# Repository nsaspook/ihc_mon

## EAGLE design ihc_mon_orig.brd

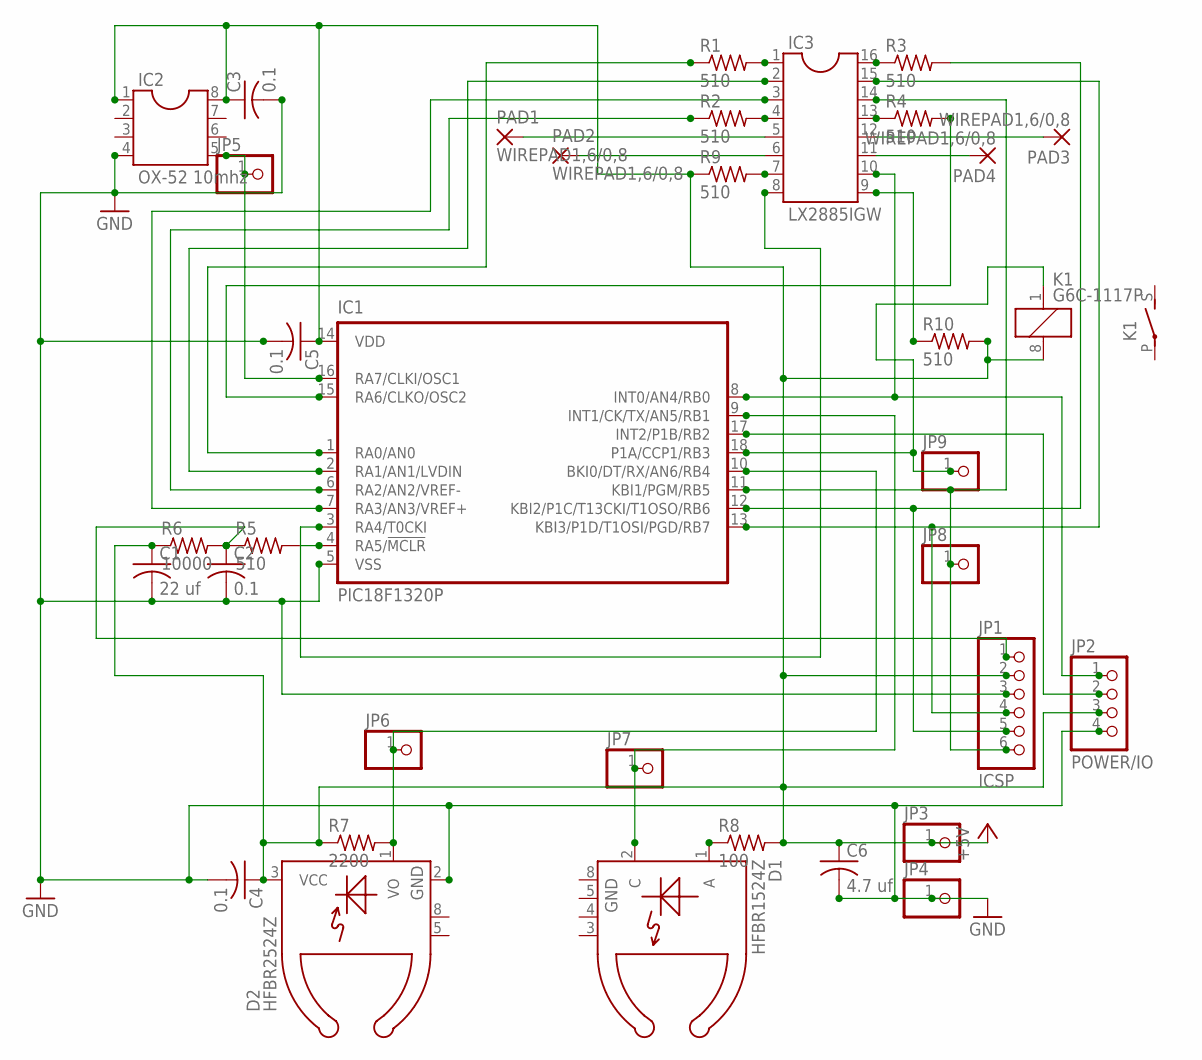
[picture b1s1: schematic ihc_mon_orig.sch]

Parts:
C1: 22 uf; C025-024X044
C2, C3, C4, C5: 0.1; C050-025X075
C6: 4.7 uf; C025-024X044
D1: HFBR1524Z; HFBR25XX
D2: HFBR2524Z; HFBR25XX
IC1: PIC18F1320P; DIL18
IC2: OX-52 10mhz; SOCKET-08
IC3: LX2885IGW; SOCKET-16
JP1: ICSP; 1X06
JP2: POWER/IO; 1X04
JP3, JP4, JP5, JP6, JP7, JP8, JP9: PINHD-1X1; 1X01
K1: G6C-1117P
PAD1, PAD2, PAD3, PAD4: WIREPAD1,6/0,8; 1,6/0,8
R1, R2, R3, R4, R5, R9, R10: 510; 0204V
R6: 10000; 0204V
R7: 2200; 0204V
R8: 100; 0204V

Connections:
+5V: C1.1, C3.1, C4.1, C5.1, C6.1, D2.3 (VCC), IC1.14 (VDD), IC2.1, IC2.8, JP1.2, JP2.3, JP3.1, K1.8 (2), R6.1, R7.1, R8.2, R9.1, R10.2
GND: C1.2, C2.2, C3.2, C4.2, C5.2, C6.2, D2.2 (GND), IC1.5 (VSS), IC2.4, JP1.3, JP2.4, JP4.1
unnamed: IC3.1, R1.2
unnamed: IC3.4, R2.2
unnamed: IC3.16, R3.1
unnamed: IC3.13, R4.1
unnamed: IC1.4 (RA5/!MCLR), R5.2
unnamed: C2.1, JP1.1, R5.1, R6.2
unnamed: D2.1 (VO), IC1.10 (BKI0/DT/RX/AN6/RB4), JP6.1, R7.2
unnamed: D1.1 (A), R8.1
unnamed: IC3.7, R9.2
unnamed: IC1.18 (P1A/CCP1/RB3), JP9.1, K1.1
unnamed: IC1.8 (INT0/AN4/RB0), IC3.10, JP2.1
unnamed: IC3.9, R10.1
unnamed: IC3.5, PAD1.1
unnamed: D1.2 (C), IC1.9 (INT1/CK/TX/AN5/RB1), JP7.1
unnamed: IC1.11 (KBI1/PGM/RB5), IC3.14, JP1.6, JP8.1
unnamed: IC1.1 (RA0/AN0), R1.1
unnamed: IC1.2 (RA1/AN1/LVDIN), IC3.2
unnamed: IC1.6 (RA2/AN2/VREF-), R2.1
unnamed: IC1.7 (RA3/AN3/VREF+), IC3.3
unnamed: IC1.12 (KBI2/P1C/T13CKI/T1OSO/RB6), JP1.5, R3.2
unnamed: IC1.13 (KBI3/P1D/T1OSI/PGD/RB7), IC3.15, JP1.4
unnamed: IC1.15 (RA6/CLKO/OSC2), R4.2
unnamed: IC3.6, PAD2.1
unnamed: IC1.3 (RA4/T0CKI), IC3.8
unnamed: IC1.16 (RA7/CLKI/OSC1), IC2.5, JP5.1
unnamed: IC1.17 (INT2/P1B/RB2), JP2.2
unnamed: IC3.12, PAD3.1
unnamed: IC3.11, PAD4.1

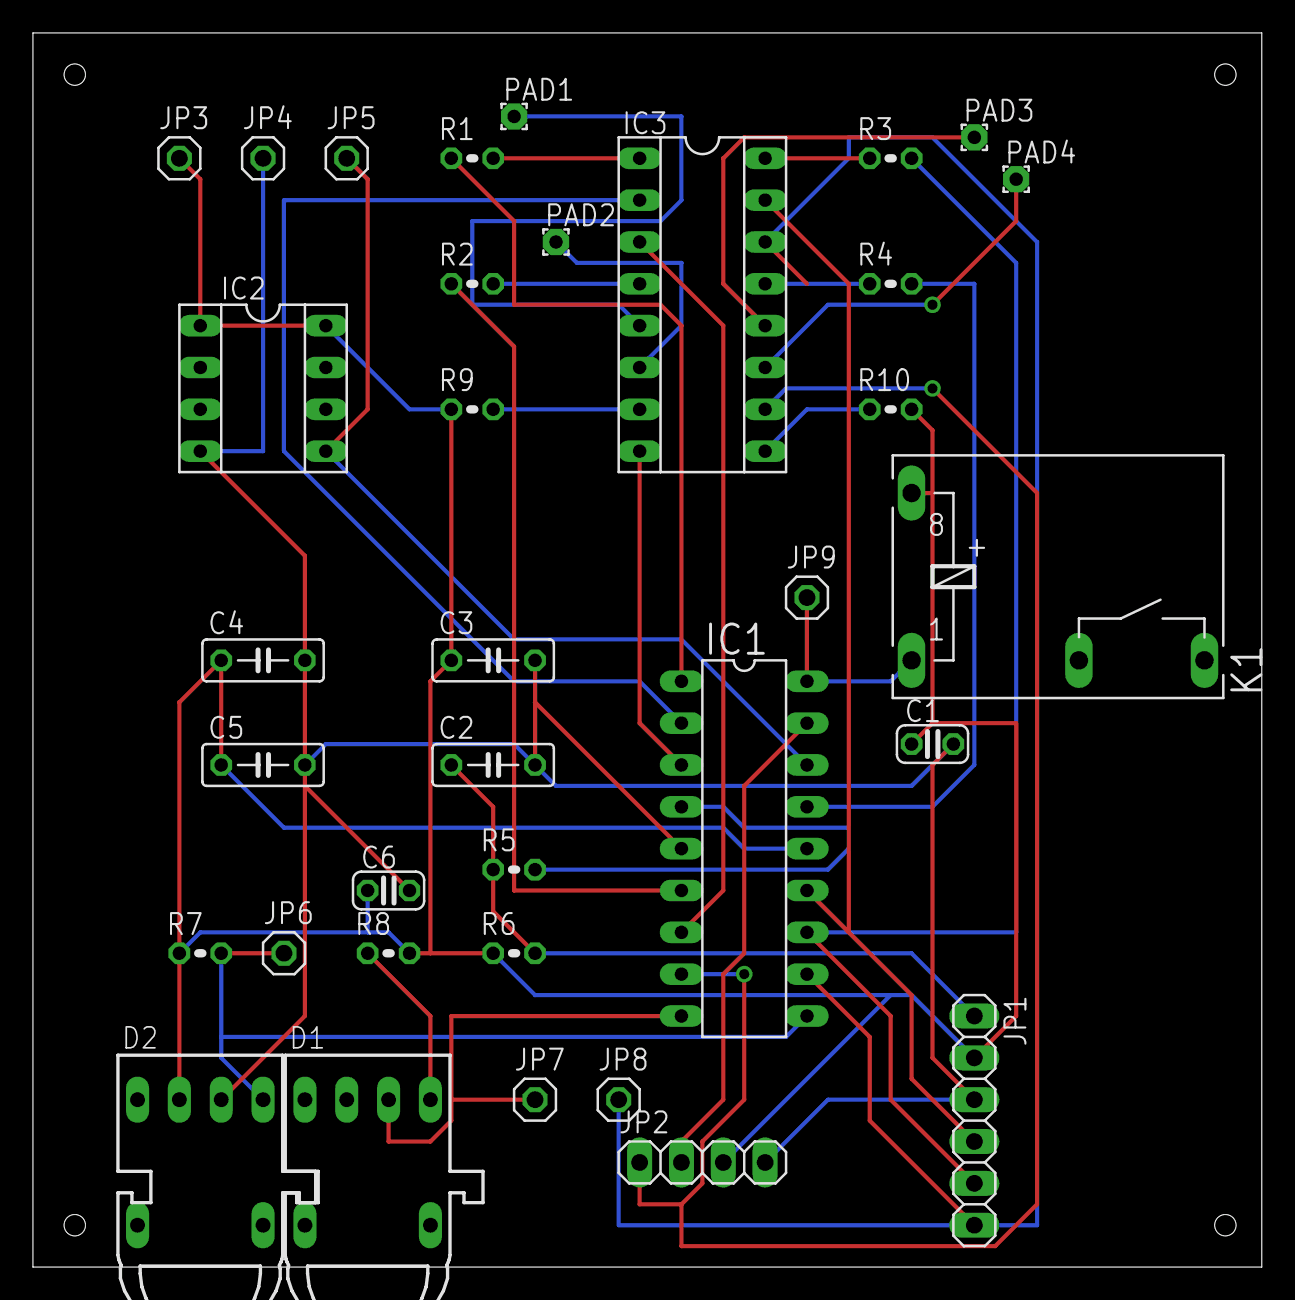
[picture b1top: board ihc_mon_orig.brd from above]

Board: 2 copper layers, 74.6 x 74.9 mm, 35 parts (0 on the bottom side), 30 nets.

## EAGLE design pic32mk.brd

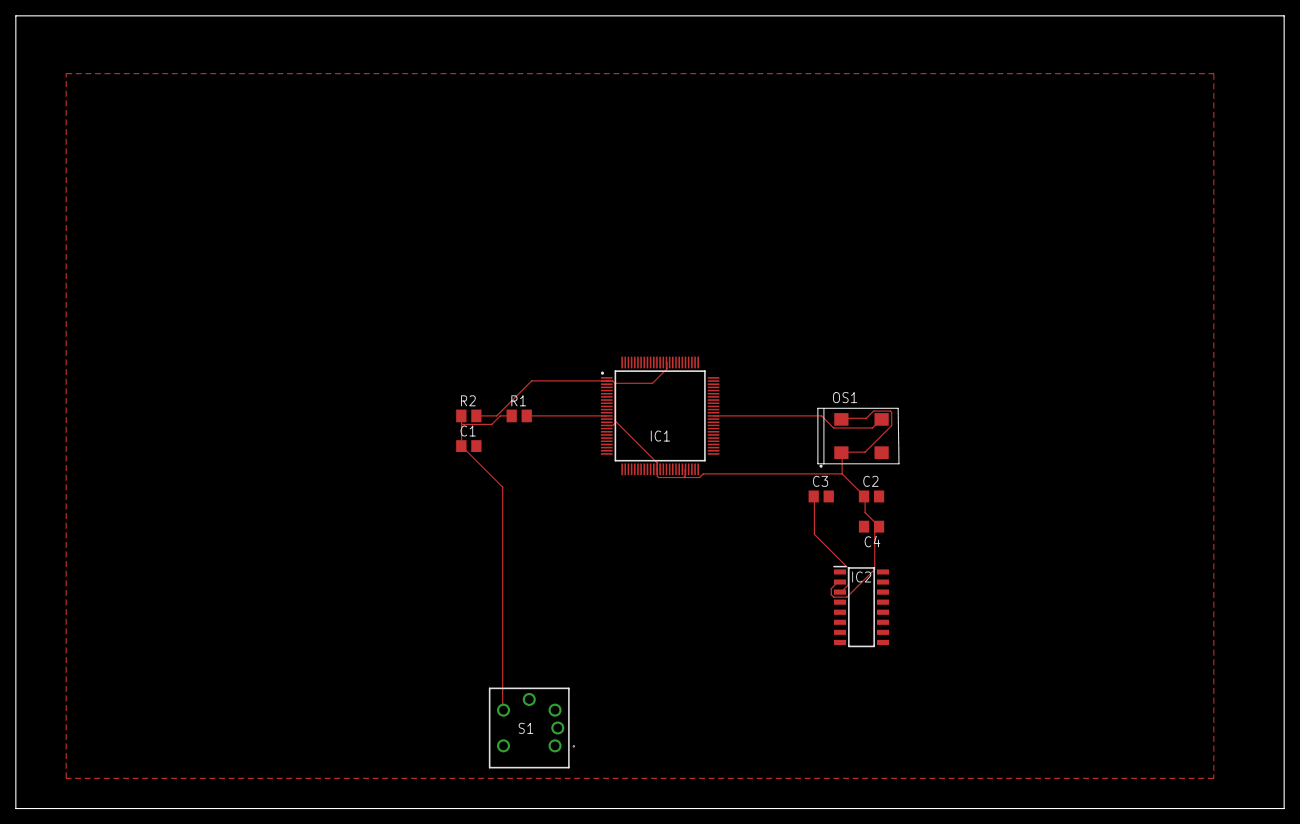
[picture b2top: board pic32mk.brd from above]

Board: 2 copper layers, 160.0 x 100.0 mm, 10 parts (0 on the bottom side), 6 nets.

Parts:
C1, C2, C3, C4: 0.1; C0805
IC1: PIC32MK1024MCF100-I_PT; QFP40P1400X1400X120-100N
IC2: ADM3095EBRZ; SOIC127P600X175-16N
OS1: OSC-OE-CFPS-32; 7.2X5.2-4-PAD
R1: 1k; M0805
R2: 10k; M0805
S1: B3W-9000-Y1N; B3W-9_1-LED

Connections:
+5V: C3.1, IC2.3
unnamed: C1.1, R1.1, R2.1, S1.4
unnamed: IC1.13, R1.2
unnamed: IC1.63, OS1.3
VDD: C2.1, C4.1, IC1.2, IC1.16, IC1.37, IC1.46, IC1.86, IC2.2, OS1.1, OS1.4, R2.2
VSS: C1.2, C2.2, C3.2, C4.2, IC1.15, IC1.36, IC1.45, IC1.65, IC1.75, IC1.85, IC2.1, IC2.8, IC2.9, IC2.10, IC2.12, IC2.13, IC2.15, IC2.16, OS1.2, S1.2

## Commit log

2017-01-04 uploads
2017-10-23 updates to 0.7
2020-03-15 version 1.3
2020-03-25 up add xc8 branch
2020-03-25 update to xc8
